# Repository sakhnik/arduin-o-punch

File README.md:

# Arduin-o-punch

Arduino-based punching for orienteering with Mifare NFC cards.

[Facebook: ZELESTAclub](https://www.facebook.com/ZELESTAclub)

In development. The progress can be followed in the YouTube playlist:
[Arduin-o-punch](https://www.youtube.com/playlist?list=PLd7V290LAw4xda5NdMdNRS0adNVE-jHjh).

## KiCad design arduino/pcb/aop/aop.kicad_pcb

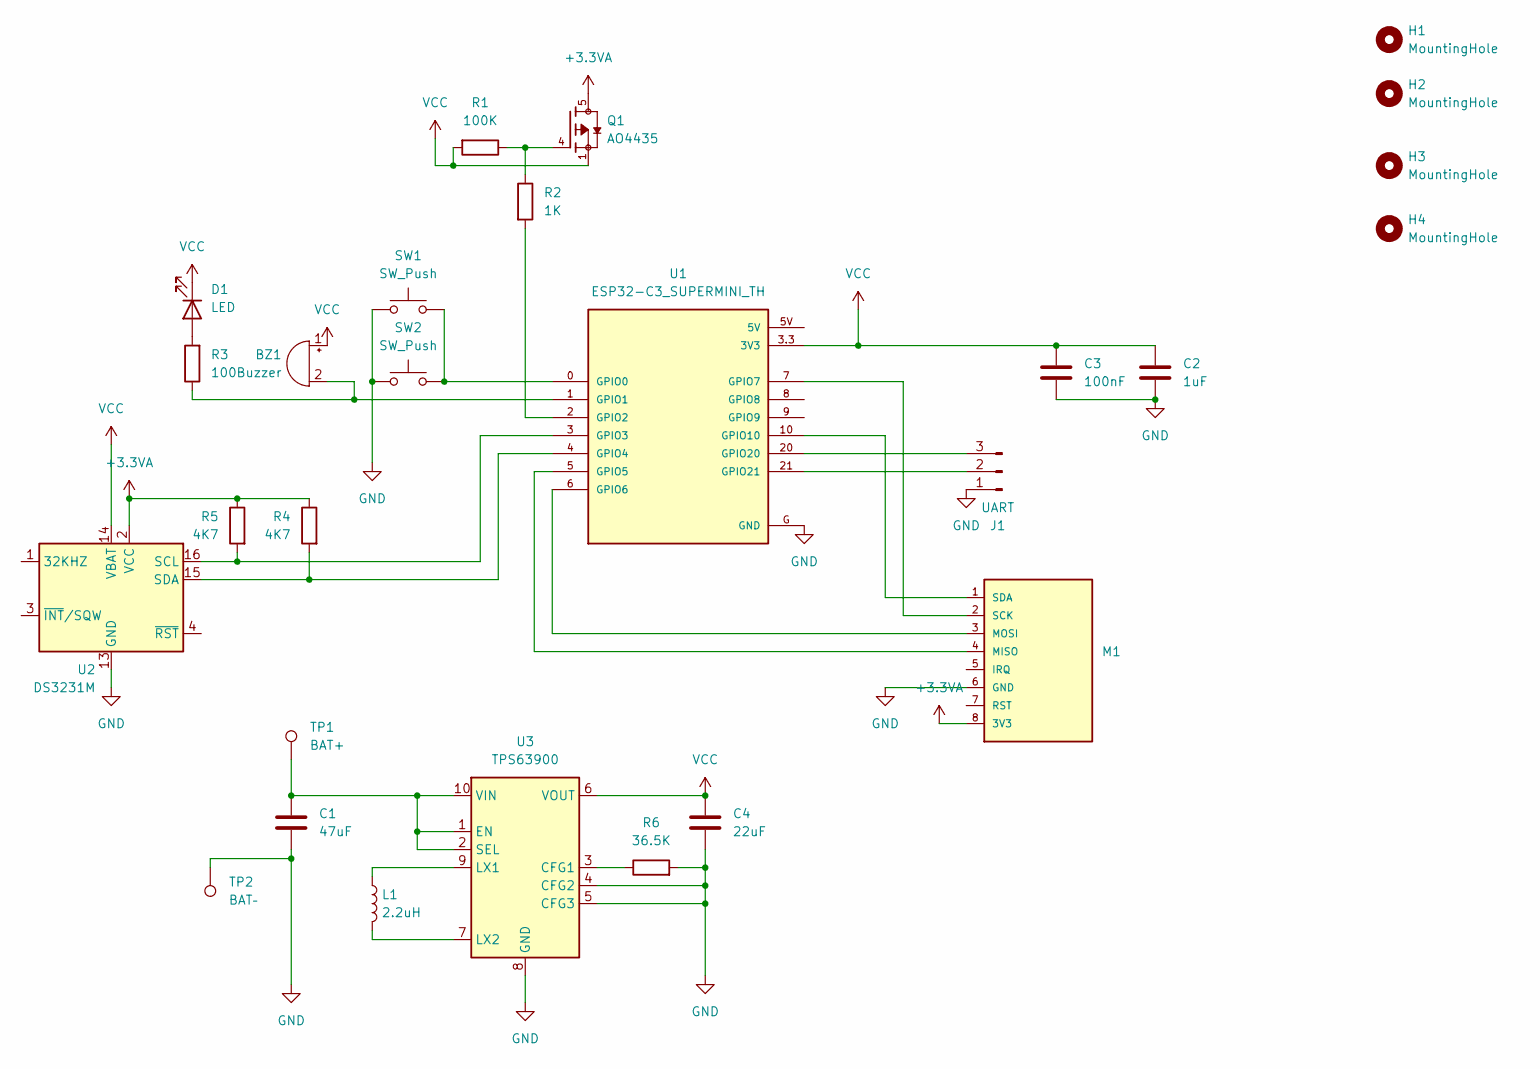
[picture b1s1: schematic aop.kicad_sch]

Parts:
BZ1: Buzzer; Buzzer_12x9.5RM7.6
C1: 47uF; C_1206_3216Metric
C2: 1uF; C_1206_3216Metric
C3: 100nF; C_1206_3216Metric
C4: 22uF; C_1206_3216Metric
D1: LED; LED_1206_3216Metric
H1, H2, H3, H4: MountingHole; MountingHole_2.2mm_M2
J1: UART; PinHeader_1x03_P2.54mm_Vertical
L1: 2.2uH; L_Changjiang_FTC404012S
M1: RFID-RC522_1; MPN RFID-RC522
Q1: AO4435; SOIC127P600X175-8N
R1: 100K; R_1206_3216Metric
R2: 1K; R_1206_3216Metric
R3: 100; R_1206_3216Metric
R4, R5: 4K7; R_1206_3216Metric
R6: 36.5K; C_0805_2012Metric
SW1: SW_Push; R_Axial_DIN0207_L6.3mm_D2.5mm_P5.08mm_Vertical
SW2: SW_Push; R_Axial_DIN0207_L6.3mm_D2.5mm_P15.24mm_Horizontal
TP1: BAT+; TestPoint_THTPad_4.0x4.0mm_Drill2.0mm
TP2: BAT–; TestPoint_THTPad_4.0x4.0mm_Drill2.0mm
U1: ESP32-C3_SUPERMINI_TH; MODULE_ESP32-C3_SUPERMINI_TH
U2: DS3231M; SOIC-16W_7.5x10.3mm_P1.27mm
U3: TPS63900; WSON-10-1EP_2.5x2.5mm_P0.5mm_EP1.2x2mm_ThermalVias

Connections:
+3.3VA: M1.8 (3V3), Q1.5, Q1.6, Q1.7, Q1.8, R4.1, R5.1, U2.2 (VCC)
GND: C1.2, C2.2, C3.2, C4.2, J1.1, M1.6 (GND), R6.2, SW1.1, SW2.1, TP2.1 (1_1), U1.G (GND), U2.5 (GND), U2.6 (GND), U2.7 (GND), U2.8 (GND), U2.9 (GND), U2.10 (GND), U2.11 (GND), U2.12 (GND), U2.13 (GND), U3.4 (CFG2), U3.5 (CFG3), U3.8 (GND), U3.11 (GND)
unnamed: BZ1.2 (-), R3.1, U1.1 (GPIO1)
unnamed: D1.2 (A), R3.2
unnamed: J1.2, U1.21 (GPIO21)
unnamed: J1.3, U1.20 (GPIO20)
unnamed: M1.4 (MISO), U1.5 (GPIO5)
unnamed: M1.3 (MOSI), U1.6 (GPIO6)
unnamed: M1.2 (SCK), U1.7 (GPIO7)
unnamed: M1.1 (SDA), U1.10 (GPIO10)
unnamed: Q1.4, R1.1, R2.1
unnamed: SW1.2, SW2.2, U1.0 (GPIO0)
unnamed: R2.2, U1.2 (GPIO2)
unnamed: R5.2, U1.3 (GPIO3), U2.16 (SCL)
unnamed: R4.2, U1.4 (GPIO4), U2.15 (SDA)
unnamed: R6.1, U3.3 (CFG1)
unnamed: C1.1, TP1.1 (1_1), U3.1 (EN), U3.2 (SEL), U3.10 (VIN)
unnamed: L1.1, U3.9 (LX1)
unnamed: L1.2, U3.7 (LX2)
VCC: BZ1.1 (+), C2.1, C3.1, C4.1, D1.1 (K), Q1.1, Q1.2, Q1.3, R1.2, U1.3.3 (3V3), U2.14 (VBAT), U3.6 (VOUT)

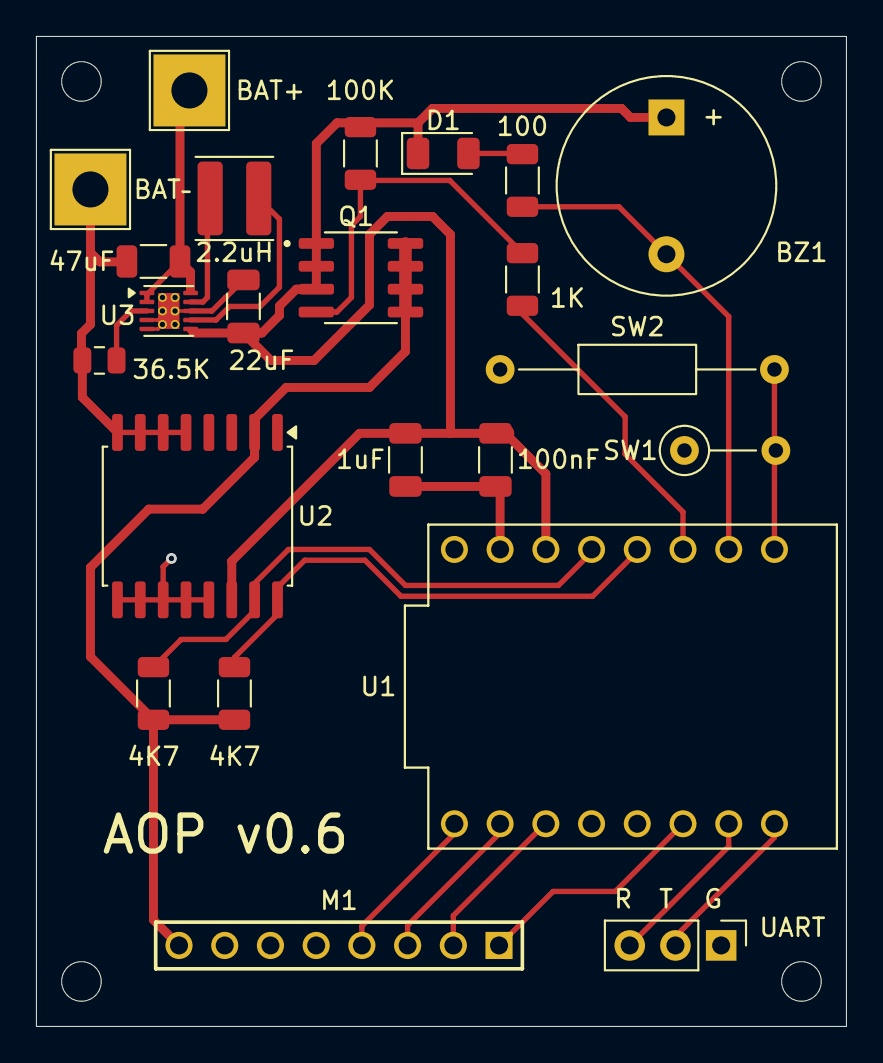
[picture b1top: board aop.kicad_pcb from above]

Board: 2 copper layers, 45.0 x 55.0 mm, 27 parts (0 on the bottom side), 20 nets.

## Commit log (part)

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2024-03-04 Allow negative timestamp differences in case the stations aren't synchronous
2024-03-04 Avoid writing to the card when the headers are valid
2024-03-05 Update the design document
2024-03-05 Fix CI failing in MSVC
2024-03-05 Revert accidental test change
2024-03-05 Fix occasional test failure
2024-03-05 Print test execution in gradle
2024-03-05 Decrease test repeatitions
2024-03-05 Revert "Print test execution in gradle"
    This reverts commit d97925c9af982436b8b9df262ef7168d4d491c98.
2024-03-06 Start test web app subproject
2024-03-07 Defined default key in IMifare
2024-03-07 Fix initialization order in Recorder
2024-03-07 Add web app built with emsdk
2024-03-07 Clear data to 0xff instead of 0 for better visibility of what's changed
2024-03-07 Fix timedelta offsets for compactness
2024-03-07 Utilize all the available space to store 184 punches
2024-03-08 Restyle the table for compactness
2024-03-08 Implement readout in wa
2024-03-09 Test compatibility of Android and Arduino with CLI
2024-03-09 Autostyle
2024-03-09 Build web app in GitHub
2024-03-10 Fix card formatting not clearing the previous punches
2024-03-10 Allow starting from sector 0
2024-03-10 Allow using all sectors in C++
2024-03-10 Add eruda for debugging
2024-03-12 Change nano profile to pro16
2024-03-14 Buy batteries
2024-03-14 Automatic DST adjustment for EEST
2024-03-15 Order more spare parts and esp32 for prototyping
2024-03-16 Add Windows instructions
2024-03-16 Add command script and --port to sync_clock.py
2024-03-19 Buy containers for stations
2024-03-19 Use external EEPROM: more size, more portable code
2024-03-20 Skip recording a duplicate punched card on the station, print error codes
2024-03-20 Track carefully whether a punch wasn't confirmed to have accurate record
2024-03-20 Fix formatting of punches in the serial log
2024-03-20 Fix record retaining period observation
2024-03-20 Allow configuring station id with sync-clock.py
2024-03-20 Fix WA: duplicate punch isn't an error
2024-03-21 Build for ESP32-C3
2024-04-07 Add OpenSCAD model of the station
2024-04-07 Add battery indicator
2024-04-07 Try designing a mount for the station
2024-04-08 Add an apron to the mount
2024-04-27 Start working on BLE #28
2024-04-27 Allow preparing card 0
2024-04-27 Intercept serial output
2024-04-28 Raise CPU frequency to 80 MHz for BLE #28
2024-04-29 Write to shell from bluetooth #28
2024-04-29 Release 2.0.0
2024-04-29 Bump version to 2.1.0
2024-04-29 Mention BT server in changelog #28
2024-04-29 Fix typing commands #28
2024-04-29 Recover 1.1.0 release date
2024-04-30 Add a ring buffer for bluetooth #28
2024-05-01 Write data to BT gradually #28
2024-05-01 Send to bluetooth independently from serial #28
2024-05-02 Order ESP32-C3
2024-05-04 Skip key in `info`
2024-05-04 Connect to a WiFi AP #35
2024-05-05 Set WiFi hostname #35
2024-05-05 Fix buzzer while initializing WiFi #35
2024-05-05 Add basic shell access at port 23
2024-05-05 Usability fixes #35
2024-05-07 Add changelog entry #35
2024-05-07 Activate access point aopNN #35
2024-05-08 Fix build in Arduino Pro Mini #35
2024-05-09 Fix promp printing via TCP #35
2024-05-09 Partially revert prompt detection #35
    Sync-clock.py brokent
2024-05-10 Fix sync-clock.py to work via TCP #35
2024-05-10 Add static web page #38
2024-05-10 Test OTA update #29
2024-05-10 Fix #29 add changelog entry
2024-05-11 Read id for web app #38
2024-05-11 Add a flask web app to facilitate development #38
2024-05-12 Configure id, key, recorder in WA #38
2024-05-12 Show and configure recorder days in the web app #38
2024-05-15 Build firmware with cmake #44
2024-05-15 Rename artifacts to remove spaces #44
2024-05-16 Take project version from CMakeLists.txt, add git revision #44
2024-05-16 Fix version insertion #44
2024-05-17 Avoid automatic formatting of html code #44
2024-05-19 Add a button to show the record #42
2024-05-20 Fix #39 Add favicon
2024-05-29 Try implementing record view #42
2024-05-29 Integrate web ui from arduin-o-punch-web-ui
2024-05-30 Remove unused serve_wa.py (web ui is developed in a separate repo)
2024-06-06 Fix #40 Implement clock synchronization in web ui
2024-07-14 Fix upload target invocation
2024-11-02 Use platformio to build firmware
2024-11-02 Ignore .pio/
2024-11-02 Fix indentation
2024-11-02 Fix wa
2024-11-02 Ignore .cache/
2024-11-02 Fix cmake jobs
2024-11-02 Build with pio in github workflow
2024-11-03 Fix android puncher test
2024-11-03 Update changelog
2024-11-03 Remove unused variable now
2024-11-03 Fix compilation warning of left shift
2024-11-03 Extract data into a simple structure for offsetof
2024-11-05 Enable jetpack compose #48
2024-11-05 Create screens and navigation
2024-11-06 Format card #48
2024-11-07 Port clear, punch, reset
2024-11-08 Remove arduino-cli remains
2024-11-09 Port format screen to compose
2024-11-11 Introduce preferences repository
2024-11-11 Show bottom bar on top of IME
2024-11-11 Port known keys
2024-11-11 Add a button to reveal the key
2024-11-15 Make text edits wider #48
2024-11-15 Decrease padding #48
2024-11-15 Remove unused layouts #48
2024-11-15 Fix format screen preview #48
2024-11-15 Extract common screen header #48
2024-11-15 Port punch screen #48
2024-11-15 Remove separate labels #48
2024-11-15 Port read screen #48
2024-11-15 Port reset screen #48
2024-11-16 Scan card id with QR #48
2024-11-16 Choose more conventional icons #48
2024-11-16 Fix key editing #48
2024-11-16 Debounce key editing #48
2024-11-18 Fix race when handling mifare, use fixed thread pool executor #48
2024-11-18 Update android screenshots #48
2024-11-21 Restore mockito dependency #48
2024-11-21 Upgrade dependencies #48
2024-11-23 Remove arduino-cli from usage
2024-11-24 Trim whitespaces from left to ignore \r\n in the shell
2024-11-24 Comment unused variable ms
2024-11-26 Signal last octet of IP4 address in Morse
2025-09-27 [android] Long tap on the selector fixes the function
2025-11-03 [Android] Select and copy punches to the clipboard
2025-11-04 [Arduino] print bytes of unknown command
2025-11-04 Arduino: add pro16, extract common libraries
2025-11-07 Document the inventory
2025-11-07 [Android] Remove "runner" on every page
2025-11-11 [Android] Add about dialog with version and git revision
2025-11-11 More maintenance
2025-11-11 [Android] Update settings right after import
2025-11-13 Arduino: soft reset MFRC522 periodically
2025-11-13 Arduino: debugging log puncher operation to serial
2025-11-15 [Arduino] Soft reset 522 only when the buzzer is idle
2025-11-25 Update usage.uk.md: require individual punch confirmation
2025-11-30 Prepare to release v2.1.0
2025-11-30 Update inventory
2025-11-30 Bump version to 2.2.0, prepare for future development
2025-12-14 Change license to GPL v2
2025-12-14 [PCB] Start capturing schematics
2025-12-15 PCB: start tracing
2025-12-17 One-sided tracing
2025-12-19 Ordered PCB v0.2
2025-12-28 Remove AVR support
2025-12-29 Try two-layer PCB
2026-02-14 Change default port to /dev/ttyACM0
2026-02-22 [Arduino] Experiment with deep sleep
2026-02-25 [arduino] Port Buzzer to FreeRTOS
2026-02-26 [arduino] Port Shell to FreeRTOS
2026-02-27 [arduino] Use Serial.onEvent() to avoid polling
2026-02-27 [arduino] Rename BuzzerTask to buzzer
2026-02-27 [arduino] Decrease CPU frequency to 10 MHz
2026-03-02 [arduino] Configure 10 MHz by default
2026-03-02 [arduino] Reconfigure led and buzzer pins to activate on pull down (sleep optimization)
2026-03-03 [arduino] Update schematics
2026-03-03 [arduino] Configure bus pins to high-z
2026-03-03 Try i2c for rc522
2026-03-03 Revert "Try i2c for rc522"
    This reverts commit 8de5255e3949c01a925d255cc2681ecb0f1bd34a.
2026-03-07 [arduino] Configure high impedance state for I2C and SPI => 0.3 mA
2026-03-12 [arduino] Initialize buzzer immediately after the startup
2026-03-12 [arduino] Store config in preferences instead of EEPROM
2026-03-12 [arduino] Dropped usage of external EEPROM
2026-03-12 Add TODO
2026-03-12 [arduino] Fix wrong field restoring from the preferences
2026-03-12 [arduino] Store clock in UTC
2026-03-12 [arduino] Skip I2C altogether
2026-03-14 [arduino] Disable pin hold after wakeup
2026-03-15 Remove DS3231
2026-03-15 [arduino] Upgrade MFRC522v2
2026-03-15 [arduino] Move MFRC522 into the cpp file
2026-03-18 [pcb] Add one more wakeup switch
2026-03-21 [arduino] Rework bluetooth for NimBLE
2026-03-22 [arduino] Switch CPU frequency in the control task
2026-03-22 [arduino] Increase sleep timeout to 5 minutes
2026-03-22 Keep active if a service card is punched
2026-03-22 [arduino] Get rid of BLE polling
2026-03-22 [arduino] Let the ble task kill itself
2026-03-22 [arduino] Trim whitespace from the right
2026-03-22 [arduino] Extract WiFi into own task
2026-03-23 [arduino] Add some BLE descriptors
2026-03-23 Add a ble terminal script
2026-03-23 [arduino] Fix memory leak in BLE
2026-03-24 [arduino] Fix heap corruption
2026-03-24 [arduino] Use array for key
2026-03-25 [arduino] Enable c++17
2026-03-25 [arduino] Slow down BLE transmission to avoid loosing data
2026-03-25 [arduino] Allow watching configuration changes
2026-03-25 [arduino] Expose id, key via BLE
2026-03-25 [arduino] Add a RAII mutex modelled after STL
2026-03-25 [arduino] Accept wifi password as string_view
2026-03-26 [arduino] Expose wifi params via BLE
2026-03-26 [arduino] Protect watchers from races
2026-03-26 [arduino] Protect the key
2026-03-26 [arduino] Reset BLE characteristic callbacks to avoid heap corruption
2026-03-26 [arduino] Disable astyle
2026-03-26 [arduino] Protect the rest of the config params
2026-03-27 Add Makefile for arduino development
2026-03-29 [arduino] Explore light sleep
2026-04-08 [pcb] Add battery protection to BOM
2026-04-18 [arduino] Add configurable eco mode
2026-04-18 Fix build failure with too new cmake
2026-04-19 [pcb] Restore through-hole esp32-c3
2026-04-19 [pcb] Increase the length
2026-04-19 [arduino] Configure active and eco time in the web UI
2026-04-19 [arduino] Specify timeouts in minutes for convenience
2026-04-19 [arduino] Expose timeouts via BLE
2026-04-20 [pcb] Prepare 0.2 for fabrication
2026-04-20 Add ArduinoOTA
2026-04-20 [arduino] Fix a crash when changing a setting when BLE is active
2026-04-20 [arduino] Enable OTA when WiFi is connected
2026-04-22 [arduino] Rename Context -> Settings
2026-04-22 [arduino] Record energy usage statistics
2026-04-22 Fix wasm build
2026-04-22 [arduino] Wake up for 2 minutes only (unless a card is punched), don't account service card
2026-04-23 [arduino] Add a reset reason logger
2026-04-23 [arduino] Verify RTC validity upon startup
2026-04-23 [arduino] Limit tx power
2026-04-24 [arduino] Write diagnostic information to the debug card
2026-04-24 [android] Read and display debug info
2026-04-25 [pcb] Stabilize power rail with capacitors
2026-04-25 [anrdoid] Remove excessive line from debug info
2026-04-27 [pcb] Prepare for fabrication
2026-05-02 [arduino] Restore RTC DS3231 for better precision, connect to pins 10 and 20
    The pin 9 is used for boot and it's pulled up in hardware. Bad for deep
    sleep charge economy.
2026-05-02 [pcb] Add DS3231
2026-05-03 [pcb] Choose closer pins for SPI
2026-05-03 [pcb] Reroute to improve ground plane continuity
2026-05-03 [pcb] Update BOM
2026-05-05 [pcb] Send v0.4 for fabrication
2026-05-24 [pcb] Move SDA to GPIO4 to avoid clash with UART
2026-05-25 [pcb] Rearrange pins, combine buzzer and led to free UART
2026-05-25 [pcb] Expose UART0
2026-05-26 [pcb] Send v0.5 for fabrication
2026-06-17 [arduino] build wa in make
2026-06-24 [arduino] Transition to active state when there's serial input
2026-06-24 [arduino] Fix stats printout
2026-06-24 [arduino] Dump stats with the 'log' command
2026-06-24 [arduino] Exclude more garbage chars from uart
2026-06-24 Implement readout via shell
2026-06-25 Refactor AOP lib to get rid of Arduino headers
2026-06-25 Implement card formatting
2026-06-26 Allow picking keys from the previously known ones during card formatting
2026-06-26 Update BOM
2026-06-26 Pick keys from the known ones when formatting a card
2026-06-26 Output readout to OutMux
2026-06-27 Print cardId during read out
2026-06-27 Throttle card operations when formatting and reading out
2026-06-27 Remove message about failed auth
